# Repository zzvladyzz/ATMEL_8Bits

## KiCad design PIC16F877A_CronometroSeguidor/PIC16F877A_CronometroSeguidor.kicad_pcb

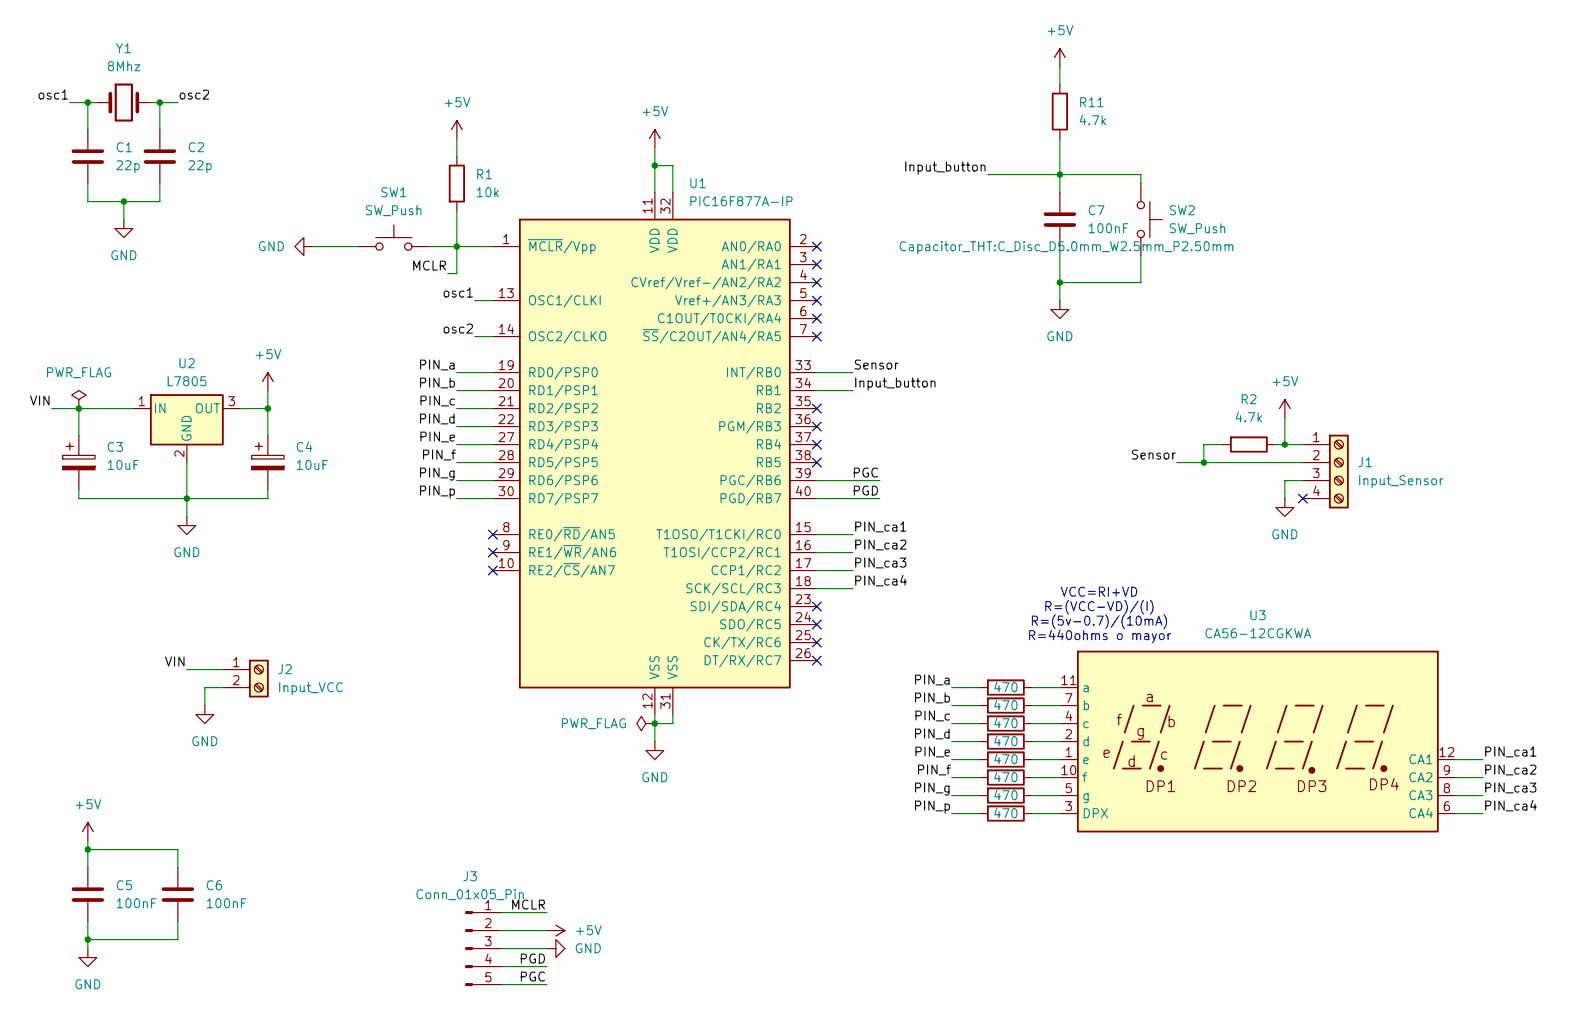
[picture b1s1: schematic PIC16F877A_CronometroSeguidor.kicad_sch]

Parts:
C1, C2: 22p; C_Disc_D5.0mm_W2.5mm_P2.50mm
C3, C4: 10uF; CP_Radial_D5.0mm_P2.00mm
C5, C6, C7: 100nF; C_Disc_D5.0mm_W2.5mm_P2.50mm
J1: Input_Sensor; TerminalBlock_MaiXu_MX126-5.0-04P_1x04_P5.00mm
J2: Input_VCC; TerminalBlock_MaiXu_MX126-5.0-02P_1x02_P5.00mm
J3: Conn_01x05_Pin; PinHeader_1x05_P2.54mm_Vertical
R1: 10k; R_Axial_DIN0207_L6.3mm_D2.5mm_P10.16mm_Horizontal
R2, R11: 4.7k; R_Axial_DIN0207_L6.3mm_D2.5mm_P10.16mm_Horizontal
R3, R4, R5, R6, R7, R8, R9, R10: 470; R_Axial_DIN0207_L6.3mm_D2.5mm_P10.16mm_Horizontal
SW1, SW2: SW_Push; SW_PUSH_6mm
U1: PIC16F877A-IP; DIP-40_W15.24mm_Socket
U2: L7805; TO-263-3_TabPin2
U3: CA56-12CGKWA
Y1: 8Mhz; Crystal_HC49-U_Vertical

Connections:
+5V: C4.1, C5.1, C6.1, J1.1, J3.2, R1.1, R2.1, R11.2, U1.11 (VDD), U1.32 (VDD), U2.3 (OUT)
/Input_button: C7.1, R11.1, SW2.1, U1.34 (RB1)
/MCLR: J3.1, R1.2, SW1.2, U1.1 (~MCLR/Vpp)
/PGC: J3.5, U1.39 (PGC/RB6)
/PGD: J3.4, U1.40 (PGD/RB7)
/PIN_a: R3.2, U1.19 (RD0/PSP0)
/PIN_b: R4.2, U1.20 (RD1/PSP1)
/PIN_c: R5.2, U1.21 (RD2/PSP2)
/PIN_ca1: U1.15 (T1OSO/T1CKI/RC0), U3.12 (CA1)
/PIN_ca2: U1.16 (T1OSI/CCP2/RC1), U3.9 (CA2)
/PIN_ca3: U1.17 (CCP1/RC2), U3.8 (CA3)
/PIN_ca4: U1.18 (SCK/SCL/RC3), U3.6 (CA4)
/PIN_d: R6.2, U1.22 (RD3/PSP3)
/PIN_e: R7.2, U1.27 (RD4/PSP4)
/PIN_f: R8.2, U1.28 (RD5/PSP5)
/PIN_g: R9.2, U1.29 (RD6/PSP6)
/PIN_p: R10.2, U1.30 (RD7/PSP7)
/Sensor: J1.2, R2.2, U1.33 (INT/RB0)
/VIN: C3.1, J2.1, U2.1 (IN)
/osc1: C1.1, U1.13 (OSC1/CLKI), Y1.1
/osc2: C2.1, U1.14 (OSC2/CLKO), Y1.2
GND: C1.2, C2.2, C3.2, C4.2, C5.2, C6.2, C7.2, J1.3, J2.2, J3.3, SW1.1, SW2.2, U1.12 (VSS), U1.31 (VSS), U2.2 (GND)
unnamed: R10.1, U3.3 (DPX)
unnamed: R3.1, U3.11 (a)
unnamed: R4.1, U3.7 (b)
unnamed: R5.1, U3.4 (c)
unnamed: R6.1, U3.2 (d)
unnamed: R7.1, U3.1 (e)
unnamed: R8.1, U3.10 (f)
unnamed: R9.1, U3.5 (g)

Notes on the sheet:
VCC=RI+VD R=(VCC-VD)/(I) R=(5v-0.7)/(10mA) R=440ohms o mayor

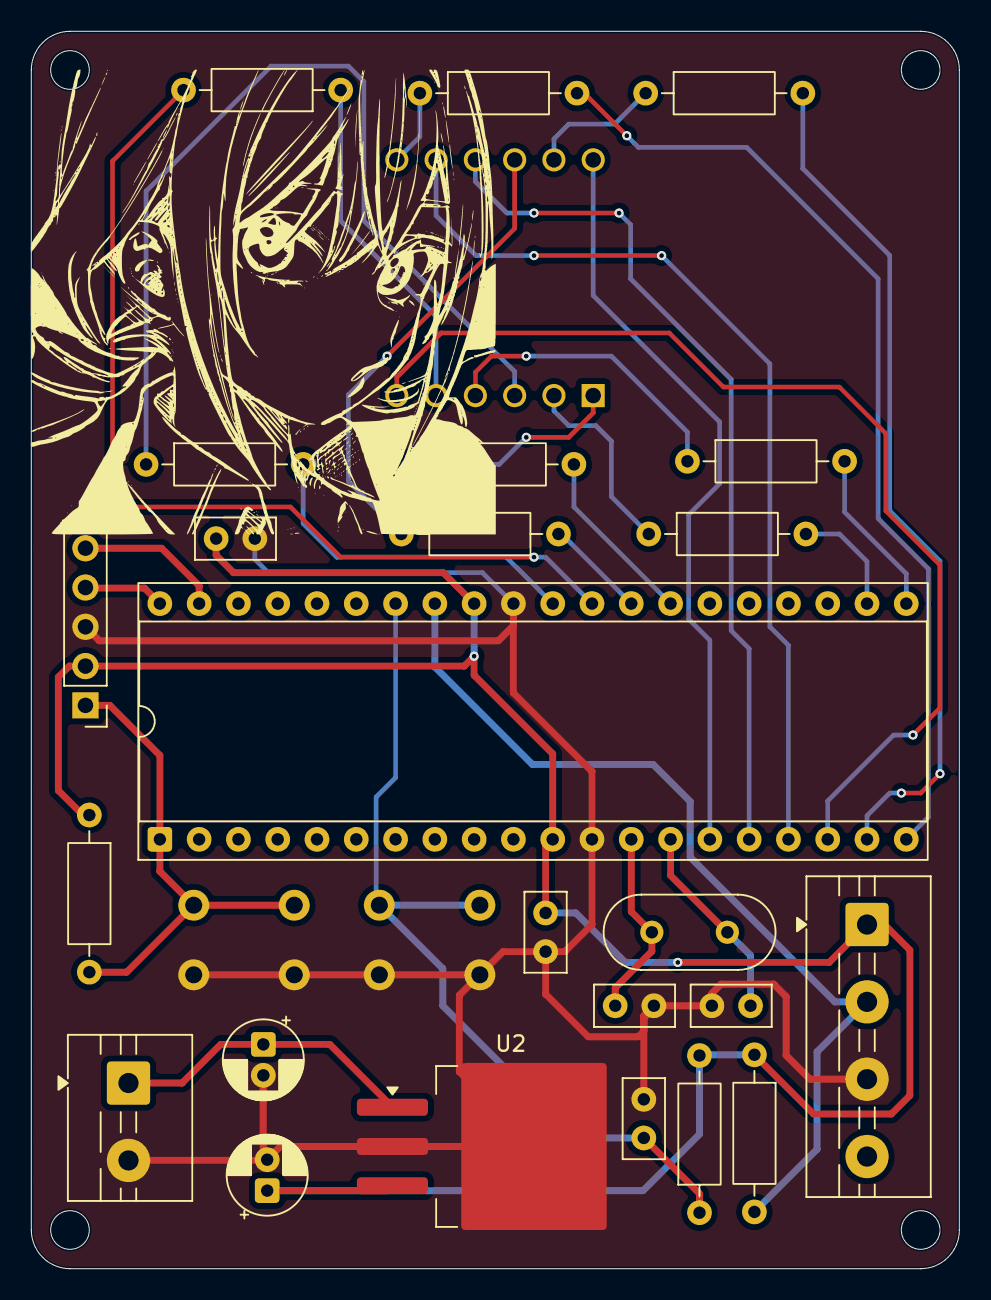
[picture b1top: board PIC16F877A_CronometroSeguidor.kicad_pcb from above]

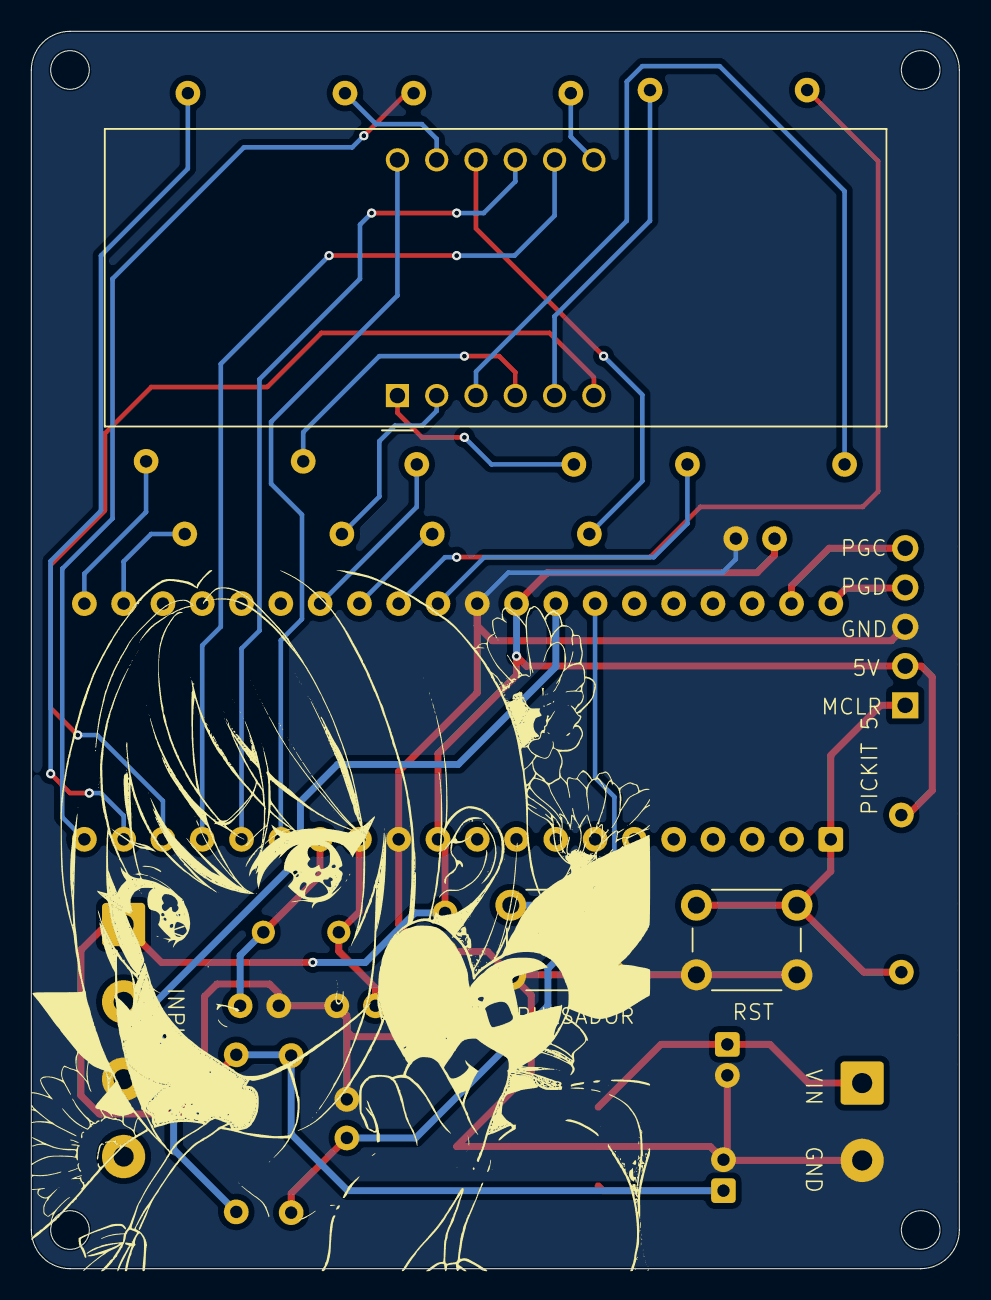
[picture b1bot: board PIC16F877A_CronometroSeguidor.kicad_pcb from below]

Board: 2 copper layers, 60.0 x 80.0 mm, 27 parts (3 on the bottom side), 30 nets.

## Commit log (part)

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2021-09-28 Proyects 9/28/2021
2021-09-28 9/28/2021
